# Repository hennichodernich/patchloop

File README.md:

# patchloop
Design files for the PatchLoop PCB

The files patchloop2.kicad_* contain the version with RJ45 jacks on opposite sides. This allows for neat short traces between the jacks.

I needed to rework the files patchloop.kicad_* (jacks on same side) because the first version contained a bug so that only one loop was used effectively.

PCB manufacturer Aisler will directly accept the KiCad file for manufacturing, but you can find zipfiles with the gerbers for both variants in the gerbers/ subdirectory. Any PCB manufacturer (e.g. BetaLayout, JLCPCB, PCBWay, OSHPark) should be able to accept those.

Licensed under CC BY-SA 3.0

# Note on the choice of balun

While in the schematic (and in the BOM) you will find an M/A-COM ETC4-1-2, this might not be the optimal choice for all possible patch cables. For cables with a length of 2-3 meters, an ETC1-1-13 usually works better to achieve ~50 ohms on the coax connector. The ETC4-1-2 is advantageous for very long cables (and thus higher impedances). I also tried Coilcraft WBC4-4 to transform from very low impedances to 50 ohms (take care of its orientation), but this only makes sense for very short cables: A 1m cable exposed approximately 10 ohms to my NanoVNA.

In general the same holds for selfwound baluns, an 1:1 balun will work best in most of your applications. For instance, I found 2:2 turns on a 9ct Fair-Rite 2843002402 binocular core working well.

Best overall performance including VLF and LF showed a M/A-COM ETC1-1T-2TR combined with 2m of S/FTP Cat6 cable.

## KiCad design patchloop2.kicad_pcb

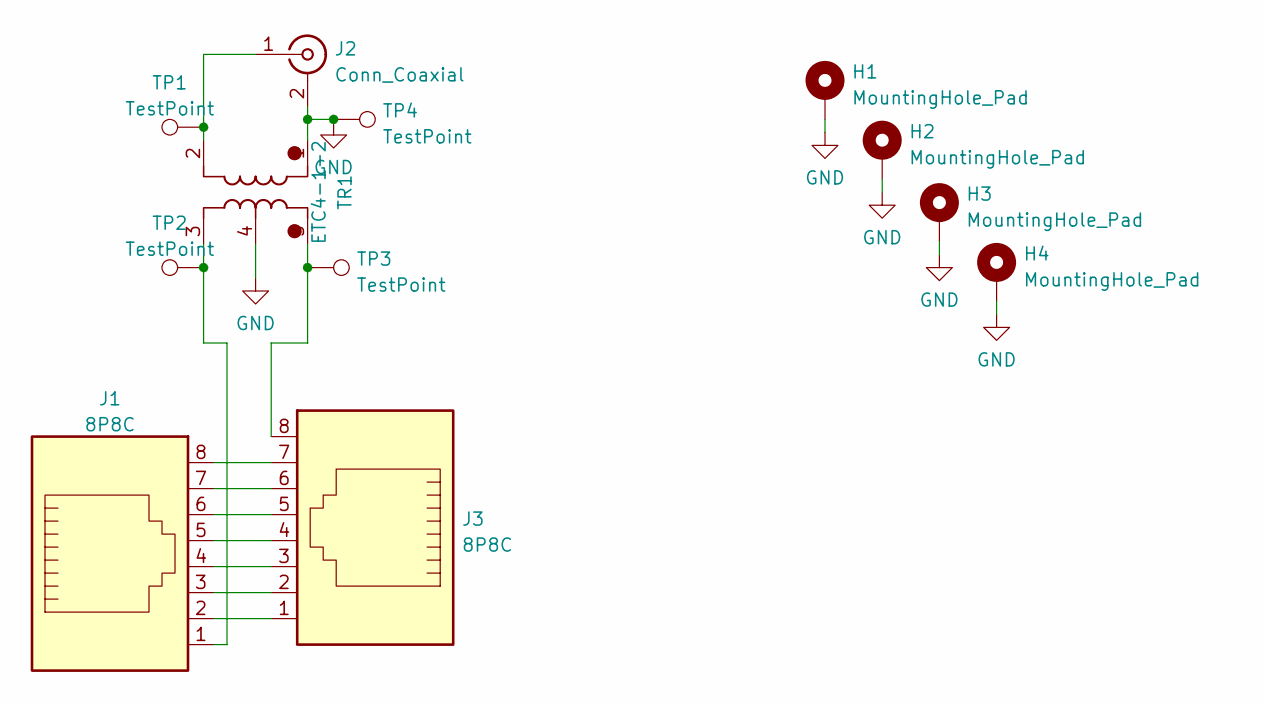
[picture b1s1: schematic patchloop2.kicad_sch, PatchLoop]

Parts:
H1, H2, H3, H4: MountingHole_Pad; MountingHole_3.2mm_M3_DIN965_Pad
J1, J3: 8P8C; RJ45_Amphenol_54602-x08_Horizontal
J2: Conn_Coaxial; SMA_Samtec_SMA-J-P-X-ST-EM1_EdgeMount
TP1, TP2, TP3, TP4: TestPoint; TestPoint_THTPad_D2.0mm_Drill1.0mm
TR1: ETC4-1-2; Transformer_MACOM_SM-22

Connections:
GND: H1.1, H2.1, H3.1, H4.1, J2.2 (Ext), TP4.1, TR1.1, TR1.4
unnamed: J1.1, TP2.1, TR1.3
unnamed: J1.2, J3.1
unnamed: J1.3, J3.2
unnamed: J1.4, J3.3
unnamed: J1.5, J3.4
unnamed: J1.6, J3.5
unnamed: J1.7, J3.6
unnamed: J1.8, J3.7
unnamed: J2.1 (In), TP1.1, TR1.2
unnamed: J3.8, TP3.1, TR1.5

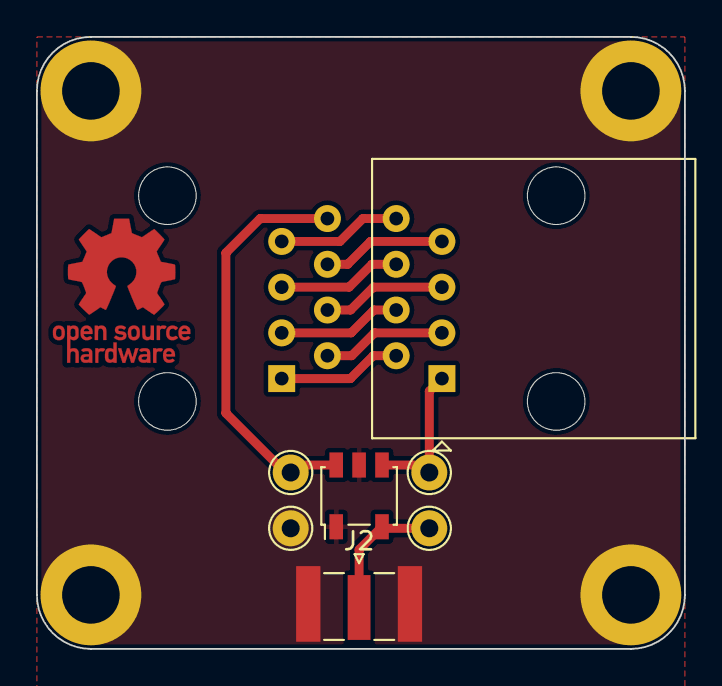
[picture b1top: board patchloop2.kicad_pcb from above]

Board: 2 copper layers, 36.0 x 34.0 mm, 12 parts (1 on the bottom side), 11 nets.

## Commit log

2023-02-25 Added license
2023-02-26 Removed non-working version
2023-02-26 Clarified README
2023-02-26 Re-added corrected version with jacks on same side
2023-02-26 Explanation in README
2023-02-26 Minor beautification update
2023-02-26 Added zipfiles for Gerbers.
2023-03-08 Added schematic
2023-06-07 Update README.md w.r.t. baluns
2023-06-08 Update README.md with balun recommendation

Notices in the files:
patchloop2.kicad_sch:
License: CC BY-SA 3.0
